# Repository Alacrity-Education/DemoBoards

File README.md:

# DemoBoards -- build up your skills

# This repo contains the files for some of the practice boards we made

## Alacrity SkillBuilder

The [Alacrity SkillBuilder](https://github.com/Alacrity-Education/DemoBoards/tree/main/SolderingSkillbuilder) board is meant to teach students the basics of soldering before they attempt the [AirBox Station](https://github.com/Alacrity-Education/AirBoxV2/tree/main) soldering. 

**BEWARE**: intentionally includes both SMD and THT components.

You can find soldering instructions and schematic [here](https://wiki.alacrity.ro/en/Courses/AirboxBootcamp/solder-training).

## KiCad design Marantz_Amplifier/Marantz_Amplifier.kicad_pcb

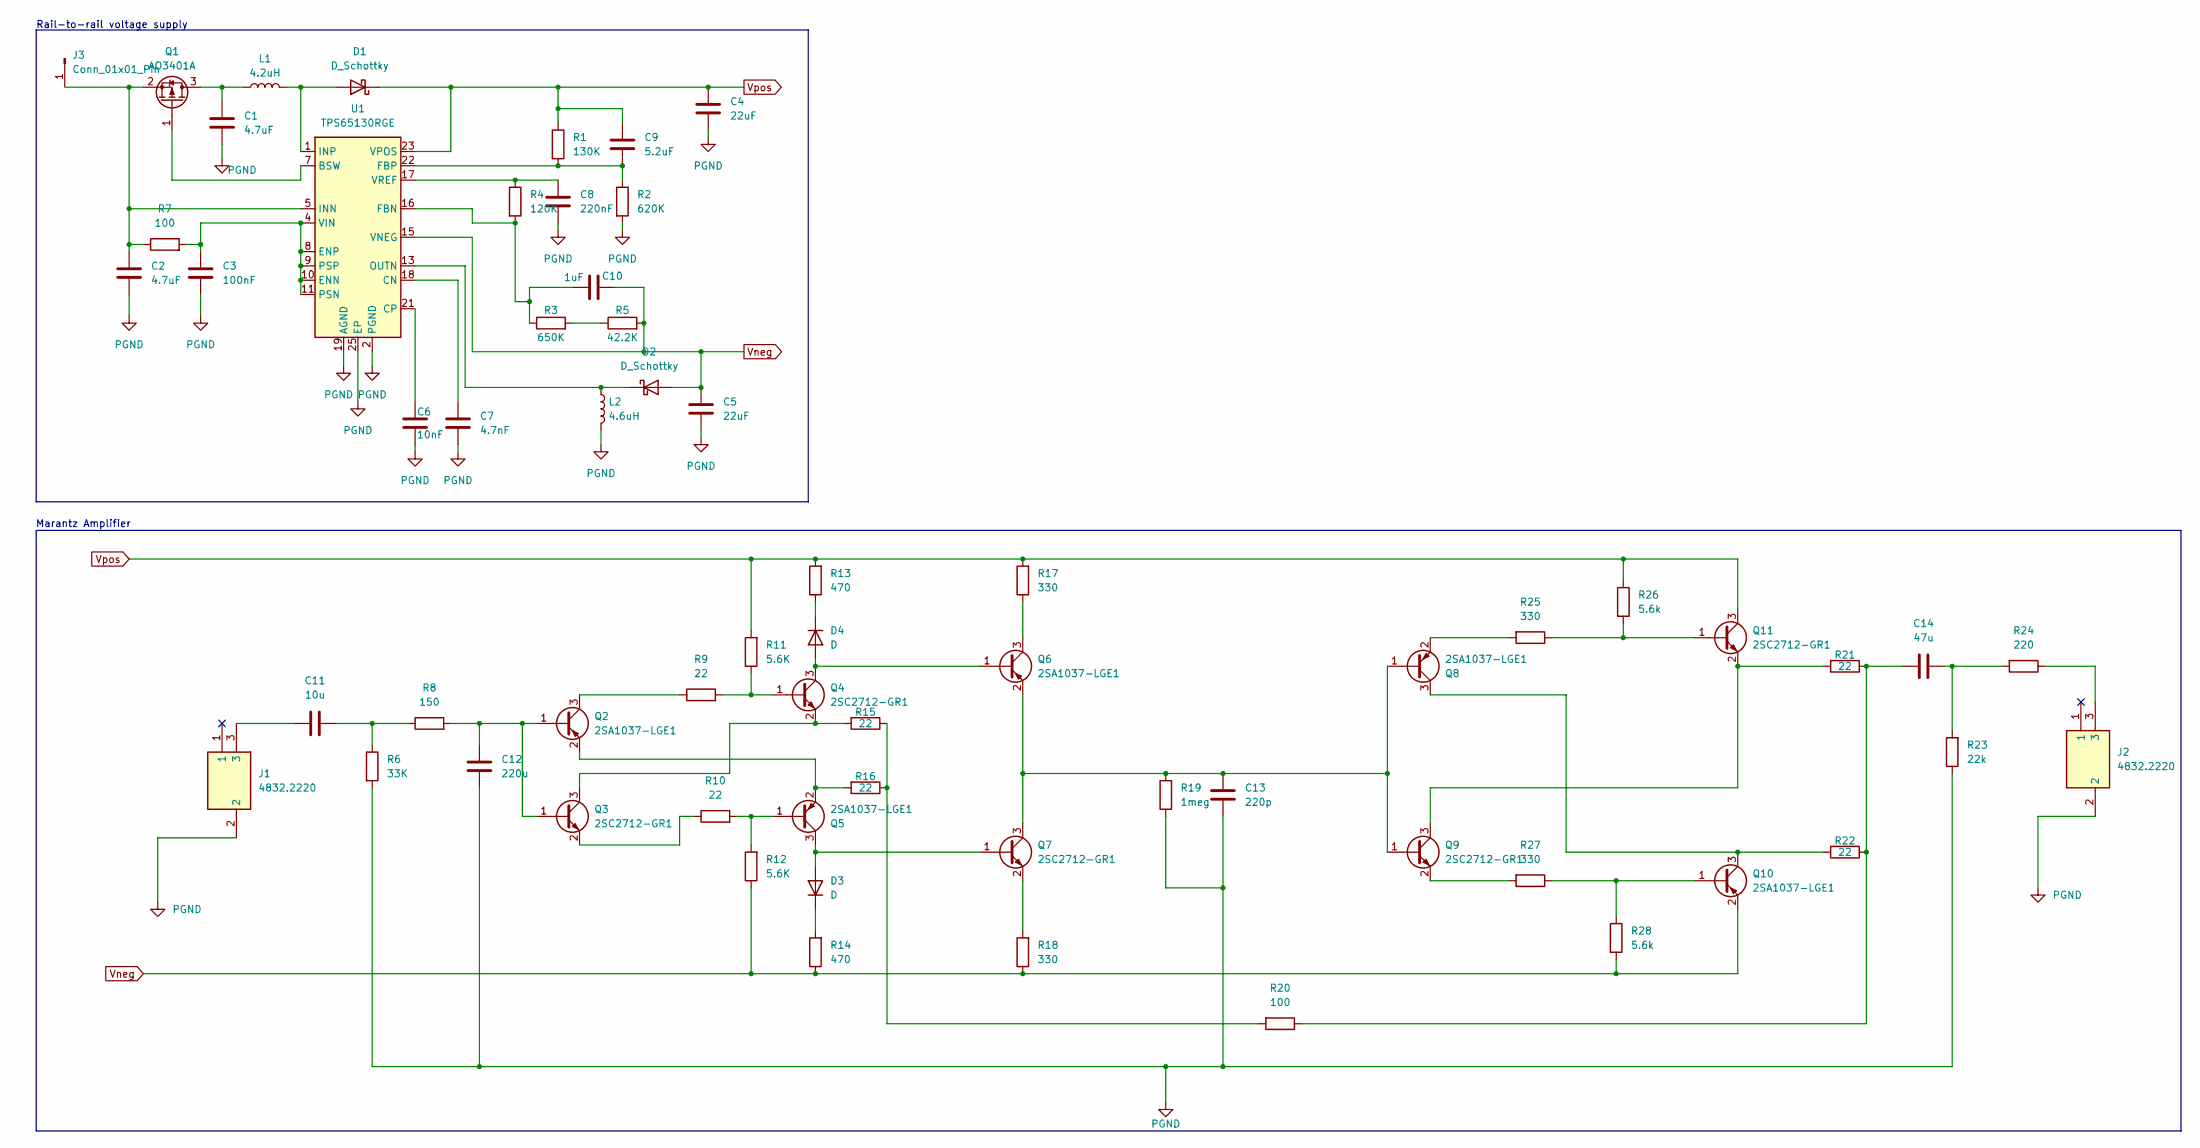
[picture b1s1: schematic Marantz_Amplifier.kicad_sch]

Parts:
C1, C2: 4.7uF; C_Elec_4x5.4
C3: 100nF; C_0805_2012Metric_Pad1.18x1.45mm_HandSolder
C4, C5: 22uF; C_Elec_6.3x5.8
C6: 10nF; C_0805_2012Metric_Pad1.18x1.45mm_HandSolder
C7: 4.7nF; C_Elec_4x5.4
C8: 220nF; C_0805_2012Metric_Pad1.18x1.45mm_HandSolder
C9: 5.2uF; EEE0JA152UAP
C10: 1uF; C_0805_2012Metric_Pad1.18x1.45mm_HandSolder
C11: 10u; C_Elec_6.3x5.4
C12: 220u; C_0805_2012Metric_Pad1.18x1.45mm_HandSolder
C13: 220p; C_0805_2012Metric_Pad1.18x1.45mm_HandSolder
C14: 47u; C_1210_3225Metric_Pad1.33x2.70mm_HandSolder
D1, D2: D_Schottky; D_SMA_Handsoldering
D3, D4: D; D_SOD-123F
J1, J2: 4832.2220; 48322220; Manufacturer_Part_Number 4832.2220; Mouser Part Number 693-4832.222
J3: Conn_01x01_Pin; PinHeader_1x01_P2.54mm_Vertical
L1: 4.2uH; L_6.3x6.3_H3
L2: 4.6uH; L_6.3x6.3_H3
Q1: AO3401A; SOT-23
Q2, Q5, Q6, Q8, Q10: 2SA1037-LGE1; SOT-23
Q3, Q4, Q7, Q9, Q11: 2SC2712-GR1; SC-59_Handsoldering
R1: 130K; R_0805_2012Metric_Pad1.20x1.40mm_HandSolder
R2: 620K; R_0805_2012Metric_Pad1.20x1.40mm_HandSolder
R3: 650K; R_0805_2012Metric_Pad1.20x1.40mm_HandSolder
R4: 120K; R_0805_2012Metric_Pad1.20x1.40mm_HandSolder
R5: 42.2K; R_0805_2012Metric_Pad1.20x1.40mm_HandSolder
R6: 33K; R_0805_2012Metric_Pad1.20x1.40mm_HandSolder
R7, R20: 100; R_0805_2012Metric_Pad1.20x1.40mm_HandSolder
R8: 150; R_0805_2012Metric_Pad1.20x1.40mm_HandSolder
R9, R10, R15, R16, R21, R22: 22; R_0805_2012Metric_Pad1.20x1.40mm_HandSolder
R11, R12: 5.6K; R_0805_2012Metric_Pad1.20x1.40mm_HandSolder
R13, R14: 470; R_0805_2012Metric_Pad1.20x1.40mm_HandSolder
R17, R18, R25, R27: 330; R_0805_2012Metric_Pad1.20x1.40mm_HandSolder
R19: 1meg; R_0805_2012Metric_Pad1.20x1.40mm_HandSolder
R23: 22k; R_0805_2012Metric_Pad1.20x1.40mm_HandSolder
R24: 220; R_0805_2012Metric_Pad1.20x1.40mm_HandSolder
R26, R28: 5.6k; R_0805_2012Metric_Pad1.20x1.40mm_HandSolder
U1: TPS65130RGE; VQFN-24-1EP_4x4mm_P0.5mm_EP2.45x2.45mm_ThermalVias

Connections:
unnamed: C11.1, J1.3
unnamed: C11.2, R6.1, R8.1
unnamed: C14.1, R23.2, R24.2
unnamed: C14.2, R20.1, R21.1, R22.1
unnamed: D1.2 (A), L1.2, U1.1 (INP), U1.24 (INP)
unnamed: D2.1 (K), L2.1, U1.13 (OUTN), U1.14 (OUTN)
unnamed: D3.2 (A), Q5.3 (C), Q7.1 (B)
unnamed: D3.1 (K), R14.2
unnamed: D4.2 (A), Q4.3 (C), Q6.1 (B)
unnamed: D4.1 (K), R13.1
unnamed: J2.3, R24.1
unnamed: C2.2, J3.1 (Pin_1_1), Q1.2 (S), R7.1, U1.5 (INN), U1.6 (INN)
unnamed: C1.1, L1.1, Q1.3 (D)
unnamed: Q1.1 (G), U1.7 (BSW)
unnamed: C12.2, Q2.1 (B), Q3.1 (B), R8.2
unnamed: Q2.3 (C), R9.1
unnamed: Q2.2 (E), Q5.2 (E), R16.2
unnamed: Q3.3 (C), Q4.2 (E), R15.2
unnamed: Q3.2 (E), R10.1
unnamed: Q4.1 (B), R9.2, R11.1
unnamed: Q5.1 (B), R10.2, R12.2
unnamed: Q6.3 (C), R17.1
unnamed: C13.2, Q6.2 (E), Q7.3 (C), Q8.1 (B), Q9.1 (B), R19.2
unnamed: Q7.2 (E), R18.2
unnamed: Q8.2 (E), R25.2
unnamed: Q9.2 (E), R27.2
unnamed: Q10.1 (B), R27.1, R28.1
unnamed: Q8.3 (C), Q10.3 (C), R22.2
unnamed: Q11.1 (B), R25.1, R26.2
unnamed: Q9.3 (C), Q11.2 (E), R21.2
unnamed: R3.2, R5.1
unnamed: R15.1, R16.1, R20.2
unnamed: C7.2, U1.18 (CN)
unnamed: C6.2, U1.21 (CP)
unnamed: C3.2, R7.2, U1.4 (VIN), U1.8 (ENP), U1.9 (PSP), U1.10 (ENN), U1.11 (PSN)
unnamed: C10.1, R3.1, R4.2, U1.16 (FBN)
unnamed: C9.1, R1.2, R2.1, U1.22 (FBP)
unnamed: C8.2, R4.1, U1.17 (VREF)
PGND: C1.2, C2.1, C3.1, C4.1, C5.1, C6.1, C7.1, C8.1, C12.1, C13.1, J1.2, J2.2, L2.2, R2.2, R6.2, R19.1, R23.1, U1.2 (PGND), U1.3 (PGND), U1.19 (AGND), U1.25 (EP)
Vneg: C5.2, C10.2, D2.2 (A), Q10.2 (E), R5.2, R12.1, R14.1, R18.1, R28.2, U1.15 (VNEG)
Vpos: C4.2, C9.2, D1.1 (K), Q11.3 (C), R1.1, R11.2, R13.2, R17.2, R26.1, U1.23 (VPOS)

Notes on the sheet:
Rail-to-rail voltage supply
Marantz Amplifier

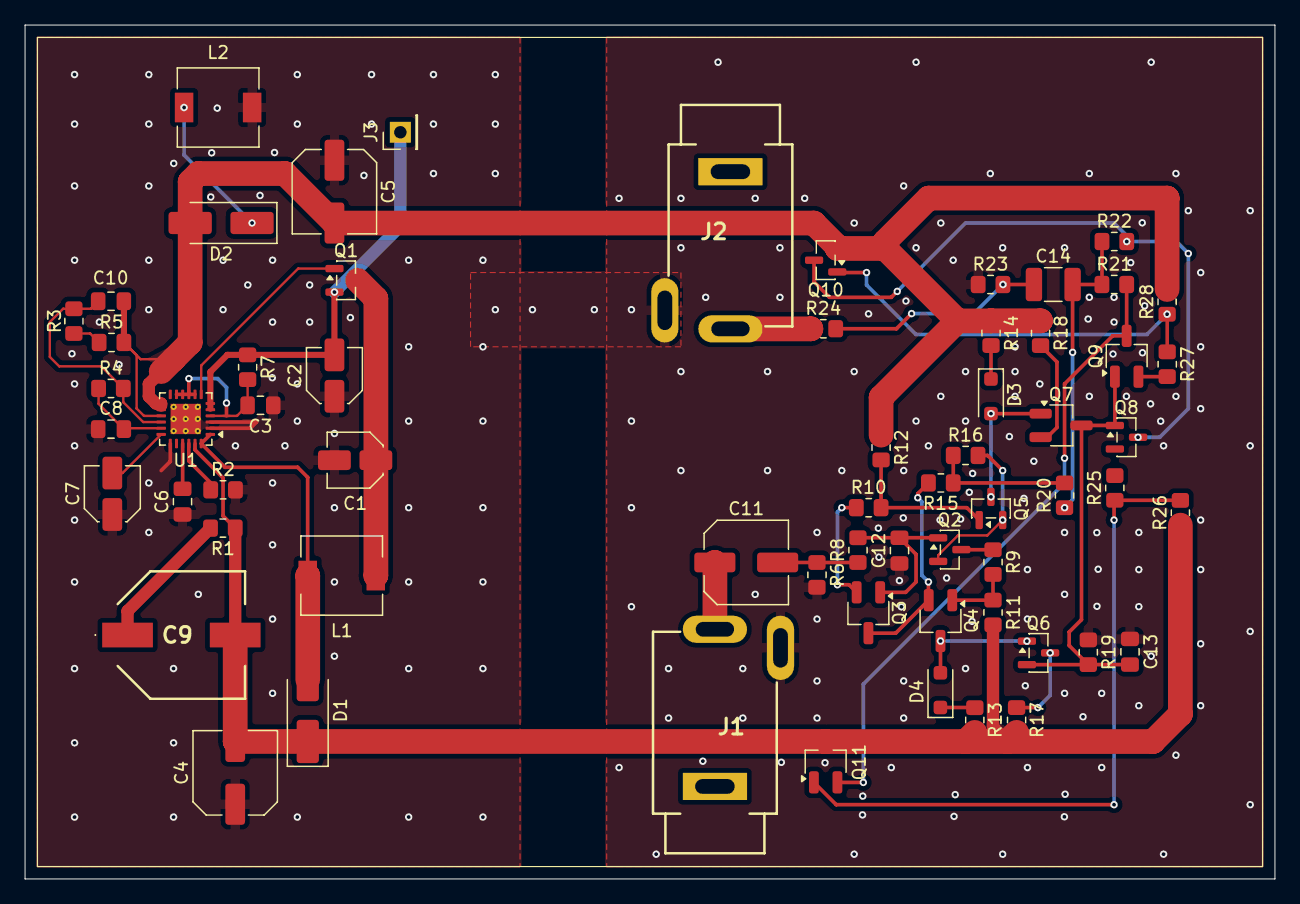
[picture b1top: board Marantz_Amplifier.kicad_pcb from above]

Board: 2 copper layers, 101.0 x 69.0 mm, 63 parts (0 on the bottom side), 41 nets.

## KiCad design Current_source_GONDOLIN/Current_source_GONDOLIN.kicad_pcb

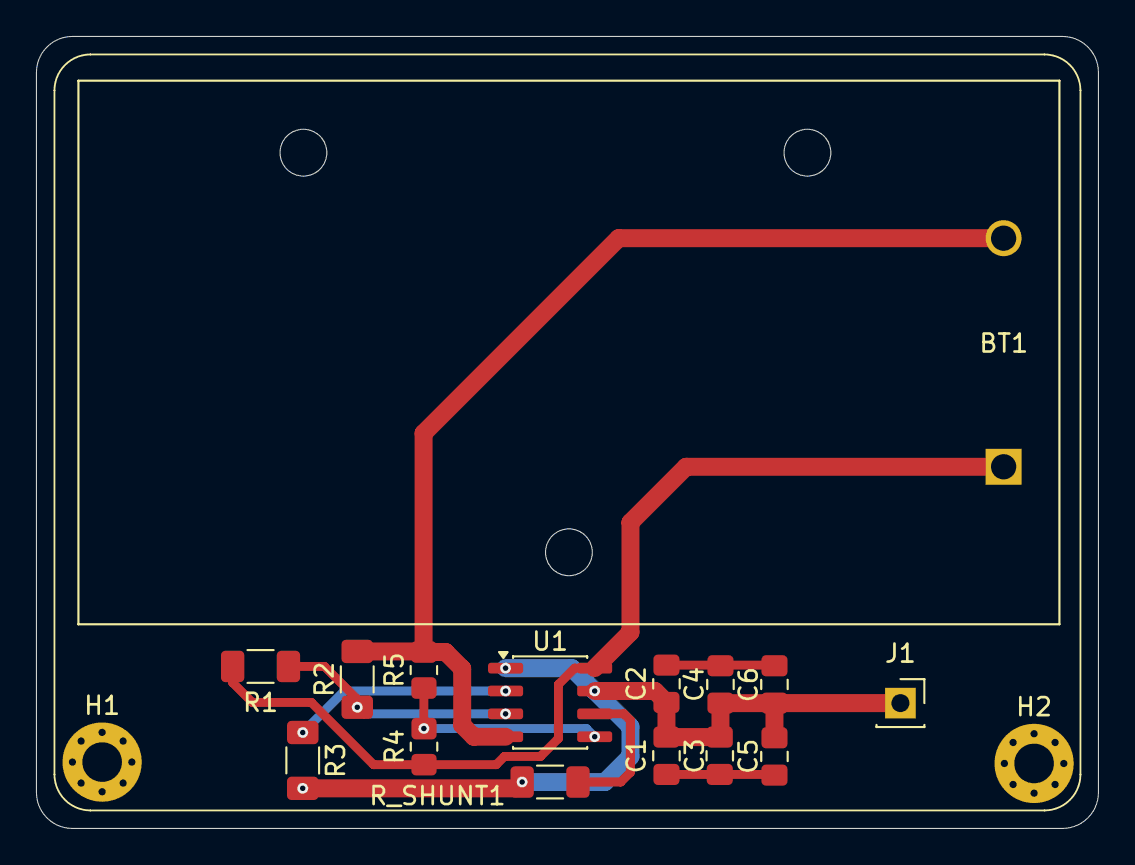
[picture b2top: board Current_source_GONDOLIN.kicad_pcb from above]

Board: 4 copper layers, 59.0 x 44.0 mm, 17 parts (0 on the bottom side), 9 nets.

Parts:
BT1: 9V; BatteryHolder_Eagle_12BH611-GR
C1, C2: 1pF; C_0805_2012Metric_Pad1.18x1.45mm_HandSolder
C3, C4: 10nF; C_0805_2012Metric_Pad1.18x1.45mm_HandSolder
C5, C6: 100uF; C_0805_2012Metric_Pad1.18x1.45mm_HandSolder
H1, H2: MountingHole_Pad; MountingHole_2.2mm_M2_Pad_Via
J1: Conn_01x01_Socket; PinSocket_1x01_P2.54mm_Vertical
R1, R2: 10K; R_1206_3216Metric_Pad1.30x1.75mm_HandSolder
R3: 10; R_1206_3216Metric_Pad1.30x1.75mm_HandSolder
R4: 6K; R_0805_2012Metric_Pad1.20x1.40mm_HandSolder
R5: 12K; R_0805_2012Metric_Pad1.20x1.40mm_HandSolder
R_SHUNT1: 300k; R_1206_3216Metric_Pad1.30x1.75mm_HandSolder
U1: TLC272; SOIC-8_3.9x4.9mm_P1.27mm

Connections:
/+9V: BT1.1 (+), R1.1, R4.1, U1.8 (V+)
/-9V: BT1.2 (-), R2.2, R5.2, U1.4 (V-)
/VGND: C1.2, C2.1, C3.2, C4.1, C5.2, C6.1, H1.1 (1_1), H2.1 (1_1), J1.1 (Pin_1_1), R3.2, R_SHUNT1.2, U1.1, U1.7
unnamed: C1.1, C3.1, C5.1
unnamed: C2.2, C4.2, C6.2
unnamed: R1.2, R2.1, U1.3 (+)
unnamed: R3.1, U1.2 (-)
unnamed: R4.2, R5.1, U1.5 (+)
unnamed: R_SHUNT1.1, U1.6 (-)

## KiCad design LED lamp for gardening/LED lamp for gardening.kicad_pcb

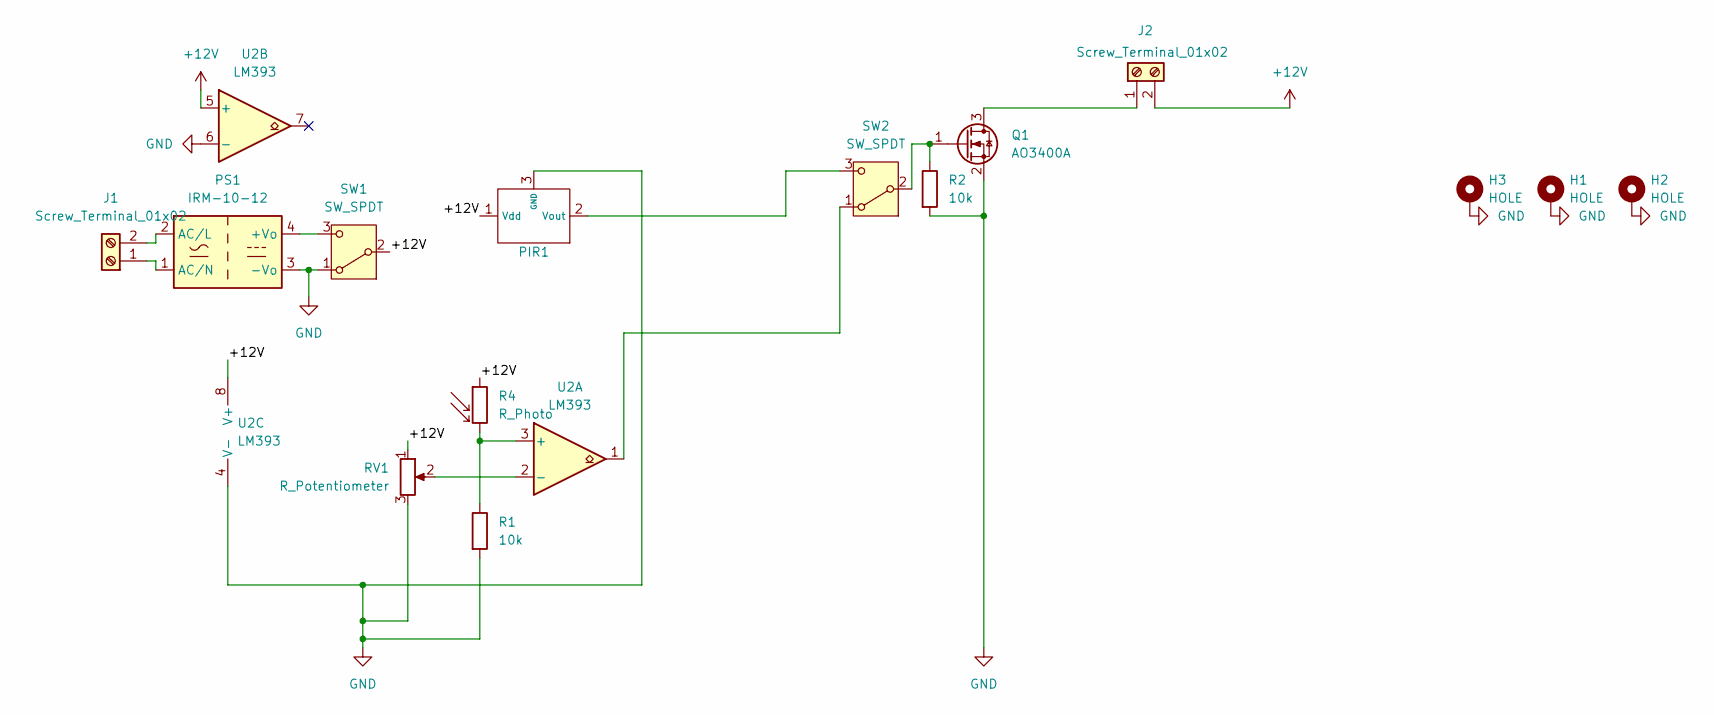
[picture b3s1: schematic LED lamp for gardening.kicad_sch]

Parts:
H1, H2, H3: HOLE; MountingHole_3.2mm_M3_Pad_Via
J1, J2: Screw_Terminal_01x02; Altech_AK300_1x02_P5.00mm_45-Degree
PIR1: PinSocket_1x03_P2.54mm_Vertical
PS1: IRM-10-12; Converter_ACDC_MeanWell_IRM-10-xx_THT
Q1: AO3400A; SOT-23
R1, R2: 10k; R_0805_2012Metric_Pad1.20x1.40mm_HandSolder
R4: R_Photo; R_LDR_4.9x4.2mm_P2.54mm_Vertical
RV1: R_Potentiometer; Potentiometer_ACP_CA9-V10_Vertical
SW1, SW2: SW_SPDT; SWITCH_BASCULANT
U2: LM393; SOIC-8_5.3x6.2mm_P1.27mm

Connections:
+12V: J2.2, PIR1.1 (Vdd), R4.1, RV1.1, SW1.2 (B), U2.5 (+), U2.8 (V+)
GND: H1.1, H2.1, H3.1, PIR1.3 (GND), PS1.3 (-Vo), Q1.2 (S), R1.2, R2.2, RV1.3, SW1.1 (A), U2.4 (V-), U2.6 (-)
unnamed: J1.1, PS1.1 (AC/N)
unnamed: J1.2, PS1.2 (AC/L)
unnamed: J2.1, Q1.3 (D)
unnamed: PIR1.2 (Vout), SW2.3 (C)
unnamed: PS1.4 (+Vo), SW1.3 (C)
unnamed: Q1.1 (G), R2.1, SW2.2 (B)
unnamed: SW2.1 (A), U2.1
unnamed: R1.1, R4.2, U2.3 (+)
unnamed: RV1.2, U2.2 (-)

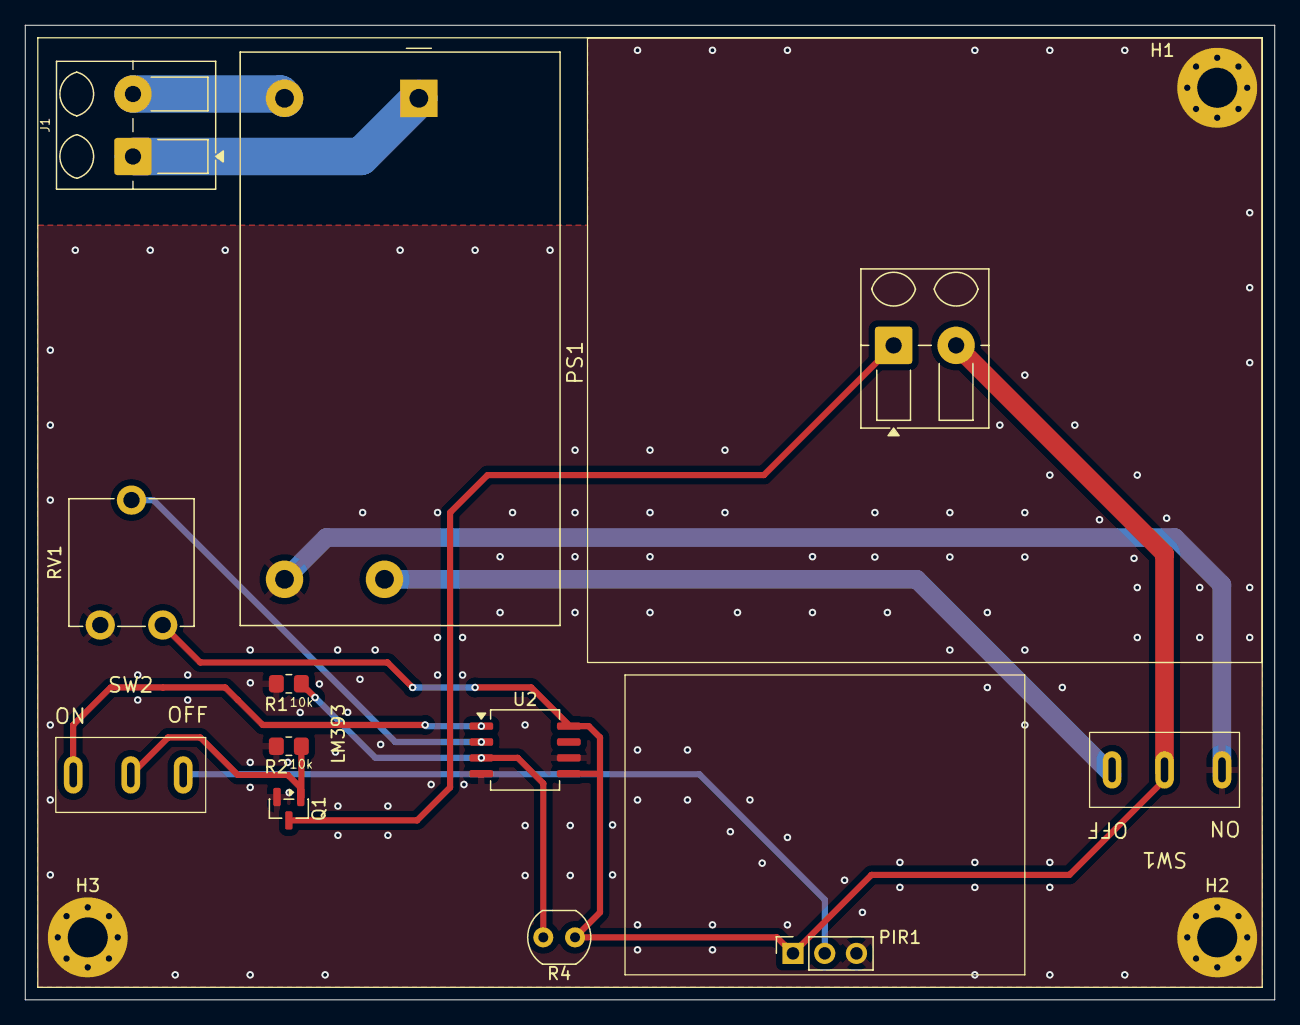
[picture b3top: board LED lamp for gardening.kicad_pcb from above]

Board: 2 copper layers, 100.0 x 78.0 mm, 15 parts (0 on the bottom side), 11 nets.

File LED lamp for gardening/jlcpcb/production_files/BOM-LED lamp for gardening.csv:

Comment,Designator,Footprint,LCSC,Quantity
Screw_Terminal_01x02,J2,Altech_AK300_1x02_P5.00mm_45-Degree,,1
LM393,U2,SOIC-8_5.3x6.2mm_P1.27mm,,1
R_Photo,R4,R_LDR_4.9x4.2mm_P2.54mm_Vertical,,1
SW_SPDT,SW2,SWITCH_BASCULANT,,1
~,PIR1,PinSocket_1x03_P2.54mm_Vertical,,1
10k,R2,R_0805_2012Metric_Pad1.20x1.40mm_HandSolder,,1
AO3400A,Q1,SOT-23,,1
IRM-10-12,PS1,Converter_ACDC_MeanWell_IRM-10-xx_THT,,1
Screw_Terminal_01x02,J1,Altech_AK300_1x02_P5.00mm_45-Degree,,1
10k,R1,R_0805_2012Metric_Pad1.20x1.40mm_HandSolder,,1
R_Potentiometer,RV1,Potentiometer_ACP_CA9-V10_Vertical,,1
SW_SPDT,SW1,SWITCH_BASCULANT,,1

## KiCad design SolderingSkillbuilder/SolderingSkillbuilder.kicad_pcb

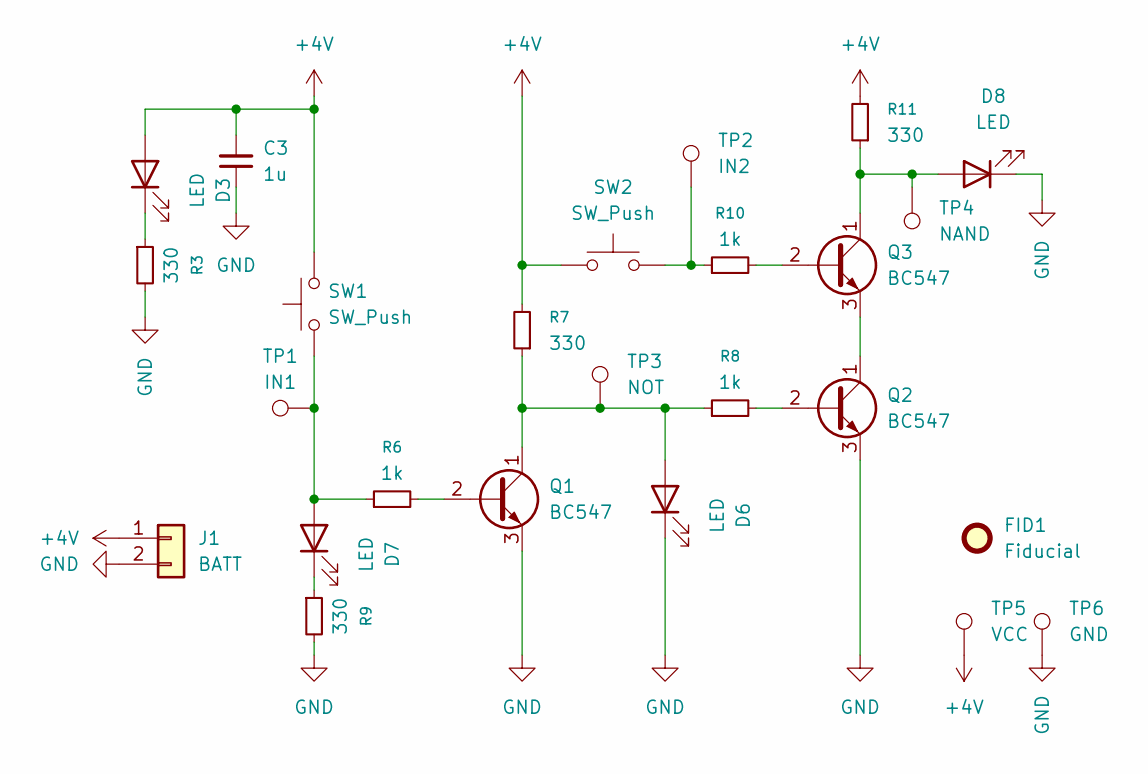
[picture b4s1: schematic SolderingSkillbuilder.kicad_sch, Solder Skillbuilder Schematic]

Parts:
C3: 1u; C_1812_4532Metric_Pad1.57x3.40mm_HandSolder
D3, D6, D7, D8: LED; LED_D3.0mm
FID1: Fiducial; Fiducial_0.5mm_Mask1.5mm
J1: BATT; JST_PH_B2B-PH-K_1x02_P2.00mm_Vertical
Q1, Q2, Q3: BC547; TO-92_Inline_Wide
R3, R7, R9, R11: 330; R_1206_3216Metric_Pad1.30x1.75mm_HandSolder
R6, R8, R10: 1k; R_1206_3216Metric_Pad1.30x1.75mm_HandSolder
SW1, SW2: SW_Push; SW_PUSH_6mm
TP1: IN1; TestPoint_Pad_D2.0mm
TP2: IN2; TestPoint_Pad_D2.0mm
TP3: NOT; TestPoint_Pad_D2.0mm
TP4: NAND; TestPoint_Pad_D2.0mm
TP5: VCC; TestPoint_Pad_D2.0mm
TP6: GND; TestPoint_Pad_D2.0mm

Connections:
+4V: C3.2, D3.2 (A), J1.1, R7.2, R11.2, SW1.2, SW2.1, TP5.1 (1_1)
GND: C3.1, D6.1 (K), D8.1 (K), J1.2, Q1.3 (E), Q2.3 (E), R3.2, R9.2, TP6.1 (1_1)
unnamed: D3.1 (K), R3.1
unnamed: D6.2 (A), Q1.1 (C), R7.1, R8.1, TP3.1 (1_1)
unnamed: D7.2 (A), R6.1, SW1.1, TP1.1 (1_1)
unnamed: D7.1 (K), R9.1
unnamed: D8.2 (A), Q3.1 (C), R11.1, TP4.1 (1_1)
unnamed: Q1.2 (B), R6.2
unnamed: Q2.2 (B), R8.2
unnamed: Q2.1 (C), Q3.3 (E)
unnamed: Q3.2 (B), R10.2
unnamed: R10.1, SW2.2, TP2.1 (1_1)

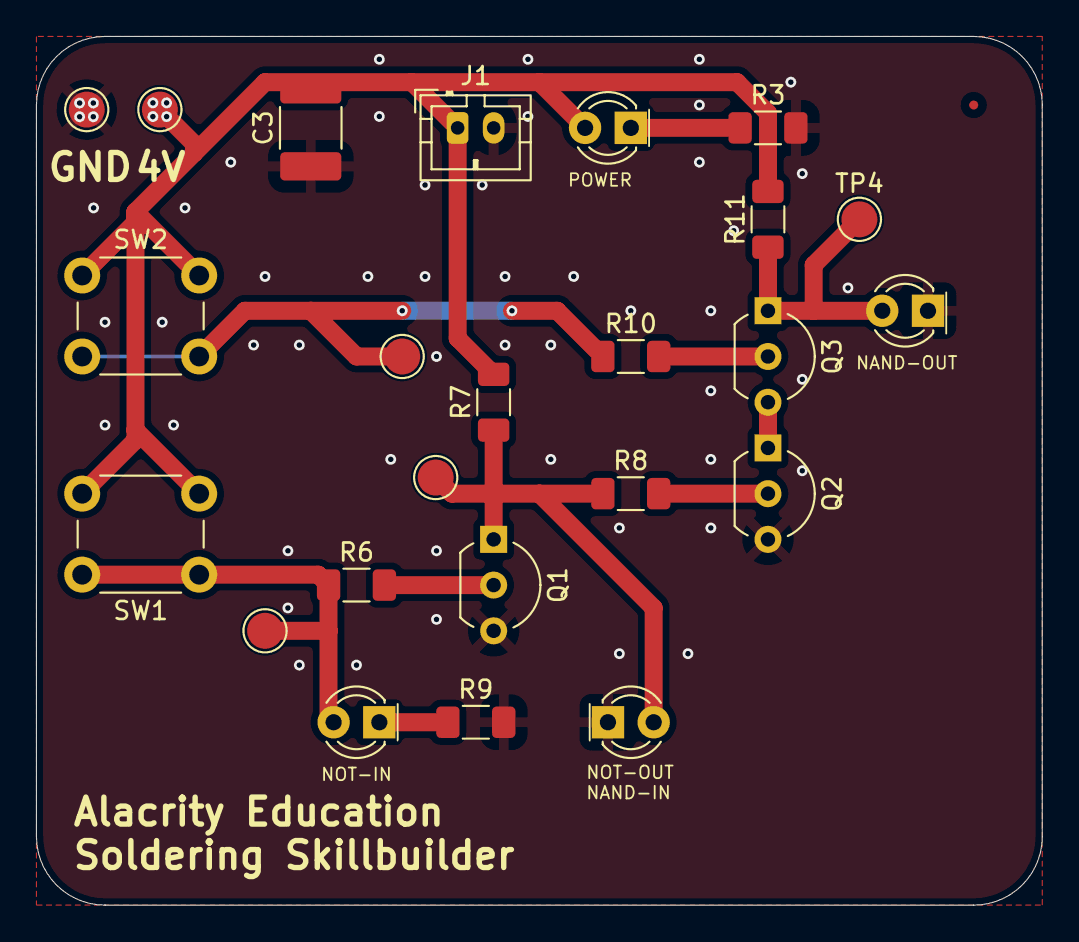
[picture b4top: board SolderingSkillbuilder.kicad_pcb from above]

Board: 2 copper layers, 55.9 x 48.3 mm, 25 parts (0 on the bottom side), 12 nets.
